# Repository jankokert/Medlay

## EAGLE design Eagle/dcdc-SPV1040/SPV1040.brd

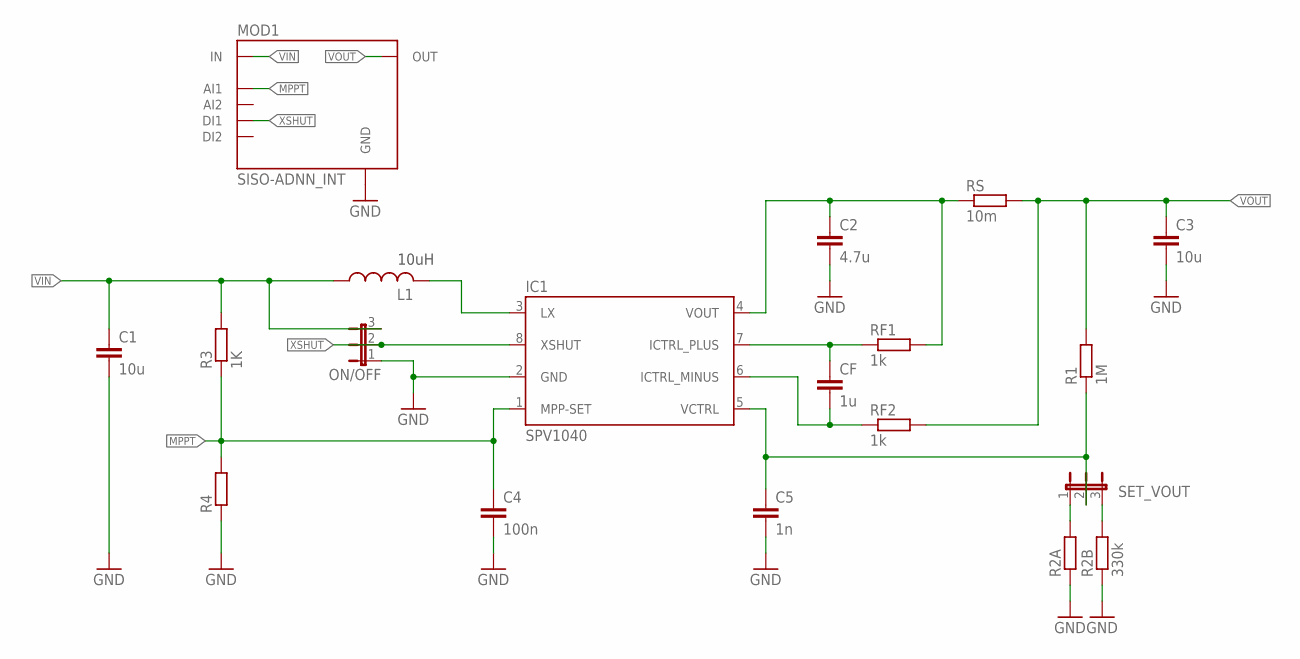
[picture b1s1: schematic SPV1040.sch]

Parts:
C1, C3: 10u; C0805
C2: 4.7u; C0805
C4: 100n; C0805
C5: 1n; C0805
CF: 1u; C0805
IC1: SPV1040; TSSOP8
L1: IHLP-2525CZ-01; 2525
MOD1: SISO-ADNN_INT; SISO-ADNN
ON/OFF: JP2E; JP2
R1: 1M; R0805
R2A, R4: R-EU_R0805; R0805
R2B: 330k; R0805
R3: 1K; R0805
RF1, RF2: 1k; R0805
RS: 10m; R0805
SET_VOUT: JP2E; JP2

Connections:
GND: C1.2, C2.2, C3.2, C4.2, C5.2, IC1.2 (GND), MOD1.GND1 (GND), MOD1.GND2 (GND), MOD1.GND3 (GND), MOD1.GND4 (GND), ON/OFF.1, R2A.1, R2B.1, R4.1
MPPT: C4.1, IC1.1 (MPP-SET), MOD1.AI1, R3.1, R4.2
unnamed: IC1.3 (LX), L1.P$1
unnamed: CF.2, IC1.6 (ICTRL_MINUS), RF2.1
unnamed: CF.1, IC1.7 (ICTRL_PLUS), RF1.1
unnamed: C2.1, IC1.4 (VOUT), RF1.2, RS.1
unnamed: C5.1, IC1.5 (VCTRL), R1.1, SET_VOUT.2
unnamed: R2A.2, SET_VOUT.1
unnamed: R2B.2, SET_VOUT.3
VIN: C1.1, L1.P$2, MOD1.IN1 (IN), MOD1.IN2 (IN), MOD1.IN3 (IN), MOD1.IN4 (IN), ON/OFF.3, R3.2
VOUT: C3.1, MOD1.OUT1_1 (OUT), MOD1.OUT1_2 (OUT), MOD1.OUT1_3 (OUT), MOD1.OUT1_4 (OUT), R1.2, RF2.2, RS.2
XSHUT: IC1.8 (XSHUT), MOD1.DI1, ON/OFF.2

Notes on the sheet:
10uH

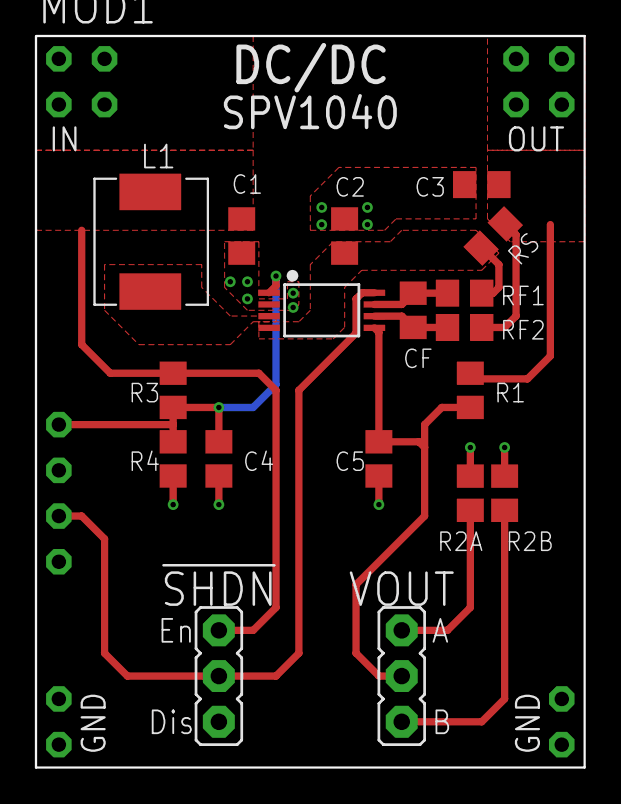
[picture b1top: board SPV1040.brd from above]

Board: 2 copper layers, 30.5 x 40.6 mm, 19 parts (0 on the bottom side), 12 nets.

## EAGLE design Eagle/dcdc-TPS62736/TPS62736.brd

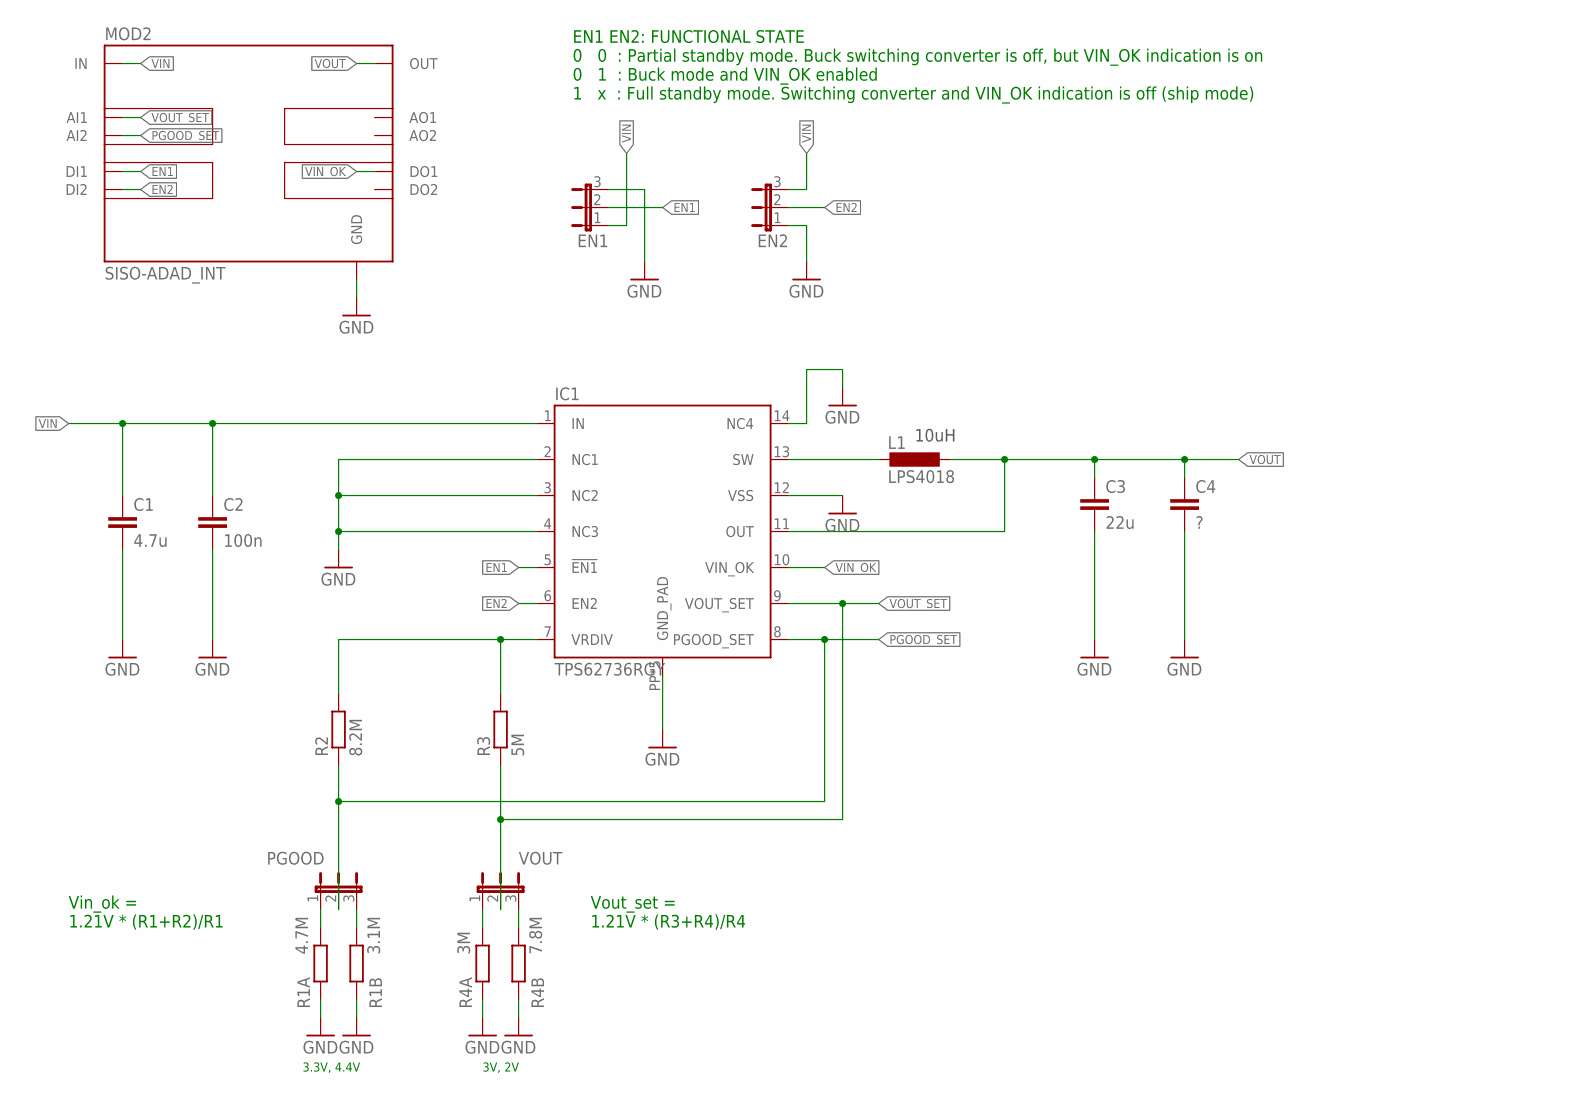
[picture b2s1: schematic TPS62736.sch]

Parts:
C1: 4.7u; C0805
C2: 100n; C0805
C3: 22u; C0805
C4: ?; C0805
EN1, EN2: JP2E; JP2
IC1: TPS62736RGY; S-PVQFN-N14
L1: LPS4018
MOD2: SISO-ADAD_INT; SISO-ADAD
PGOOD: JP2E; JP2
R1A: 4.7M; R0805
R1B: 3.1M; R0805
R2: 8.2M; R0805
R3: 5M; R0805
R4A: 3M; R0805
R4B: 7.8M; R0805
VOUT: JP2E; JP2

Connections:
EN1: EN1.2, IC1.5 (!EN1), MOD2.DI1
EN2: EN2.2, IC1.6 (EN2), MOD2.DI2
GND: C1.2, C2.2, C3.2, C4.2, EN1.3, EN2.1, IC1.2 (NC1), IC1.3 (NC2), IC1.4 (NC3), IC1.12 (VSS), IC1.14 (NC4), IC1.PP (GND_PAD), IC1.PP@1 (GND_PAD), IC1.PP@2 (GND_PAD), IC1.PP@3 (GND_PAD), IC1.PP@4 (GND_PAD), MOD2.GND1 (GND), MOD2.GND2 (GND), MOD2.GND3 (GND), MOD2.GND4 (GND), R1A.1, R1B.1, R4A.1, R4B.1
unnamed: IC1.7 (VRDIV), R2.2, R3.2
unnamed: IC1.13 (SW), L1.1
unnamed: R4A.2, VOUT.1
unnamed: R4B.2, VOUT.3
unnamed: PGOOD.1, R1A.2
unnamed: PGOOD.3, R1B.2
PGOOD_SET: IC1.8 (PGOOD_SET), MOD2.AI2, PGOOD.2, R2.1
VIN: C1.1, C2.1, EN1.1, EN2.3, IC1.1 (IN), MOD2.IN1 (IN), MOD2.IN2 (IN), MOD2.IN3 (IN), MOD2.IN4 (IN)
VIN_OK: IC1.10 (VIN_OK), MOD2.DO1
VOUT: C3.1, C4.1, IC1.11 (OUT), L1.2, MOD2.OUT1_1 (OUT), MOD2.OUT1_2 (OUT), MOD2.OUT1_3 (OUT), MOD2.OUT1_4 (OUT)
VOUT_SET: IC1.9 (VOUT_SET), MOD2.AI1, R3.1, VOUT.2

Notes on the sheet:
10uH
EN1 EN2: FUNCTIONAL STATE 0 0 : Partial standby mode. Buck switching converter is off, but VIN_OK indication is on 0 1 : Buck mode and VIN_OK enabled 1 x : Full standby mode. Switching converter and VIN_OK indication is off (ship mode)
Vin_ok = 1.21V * (R1+R2)/R1
Vout_set = 1.21V * (R3+R4)/R4
3V, 2V
3.3V, 4.4V

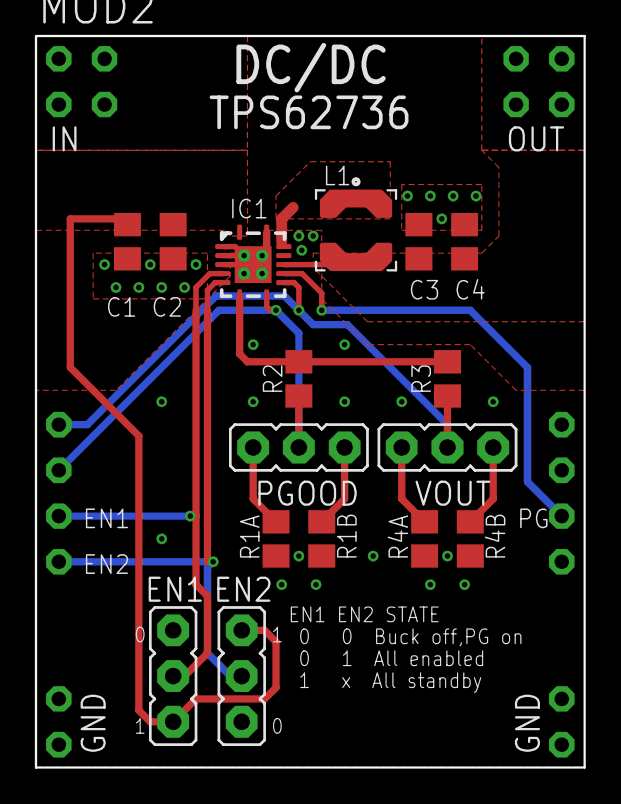
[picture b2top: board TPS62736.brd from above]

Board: 2 copper layers, 30.5 x 40.6 mm, 17 parts (0 on the bottom side), 14 nets.

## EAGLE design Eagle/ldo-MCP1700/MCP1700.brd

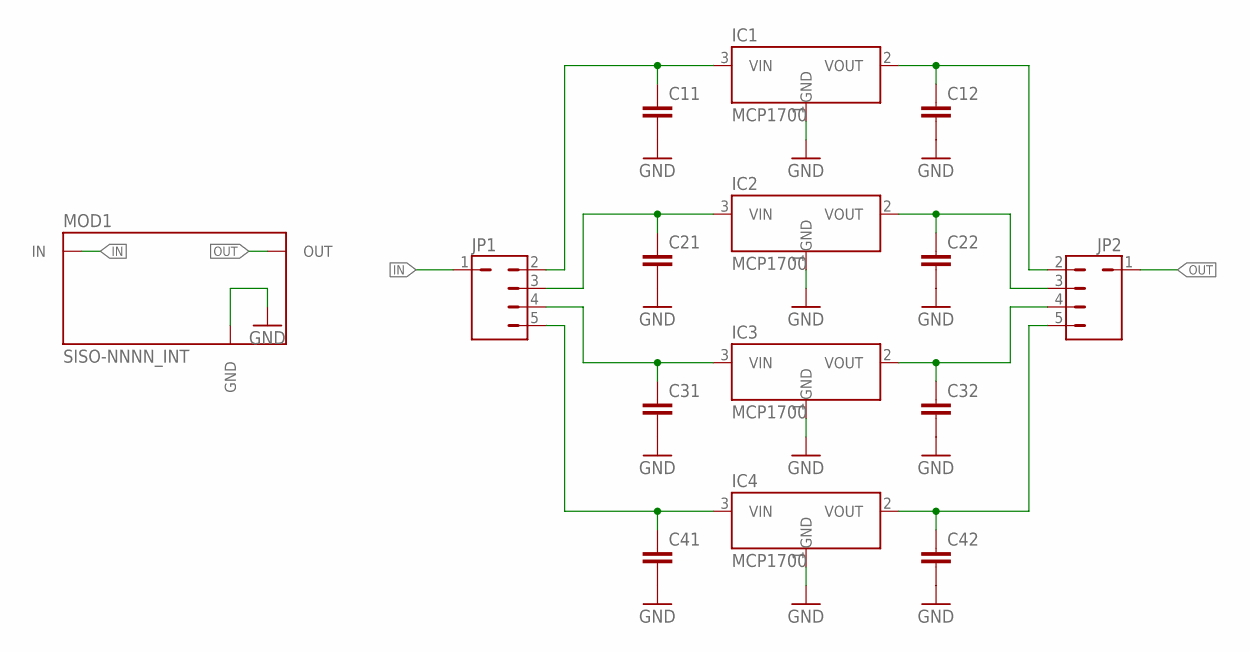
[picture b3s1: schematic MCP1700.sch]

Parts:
C11, C12, C21, C22, C31, C32, C41, C42: C-EUC0805; C0805
IC1, IC2, IC3, IC4: MCP1700; SOT23
JP1, JP2: JP4Q; JP1-4
MOD1: SISO-NNNN_INT; SISO-NNNN

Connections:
GND: C11.2, C12.2, C21.2, C22.2, C31.2, C32.2, C41.2, C42.2, IC1.1 (GND), IC2.1 (GND), IC3.1 (GND), IC4.1 (GND), MOD1.GND1 (GND), MOD1.GND2 (GND), MOD1.GND3 (GND), MOD1.GND4 (GND)
IN: JP1.1, MOD1.IN1 (IN), MOD1.IN2 (IN), MOD1.IN3 (IN), MOD1.IN4 (IN)
unnamed: C11.1, IC1.3 (VIN), JP1.2
unnamed: C21.1, IC2.3 (VIN), JP1.3
unnamed: C31.1, IC3.3 (VIN), JP1.4
unnamed: C41.1, IC4.3 (VIN), JP1.5
unnamed: C12.1, IC1.2 (VOUT), JP2.2
unnamed: C22.1, IC2.2 (VOUT), JP2.3
unnamed: C32.1, IC3.2 (VOUT), JP2.4
unnamed: C42.1, IC4.2 (VOUT), JP2.5
OUT: JP2.1, MOD1.OUT1 (OUT), MOD1.OUT2 (OUT), MOD1.OUT3 (OUT), MOD1.OUT4 (OUT)

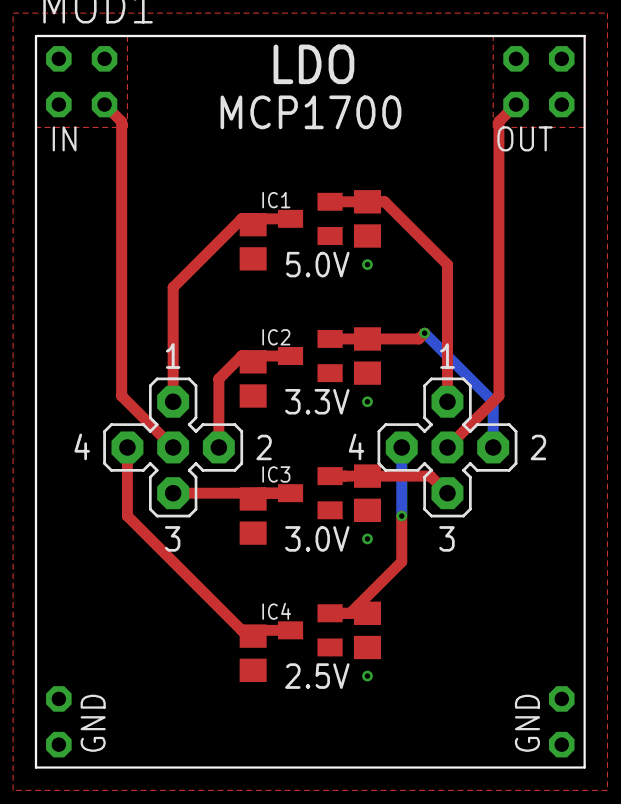
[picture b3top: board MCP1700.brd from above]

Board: 2 copper layers, 30.5 x 40.6 mm, 15 parts (0 on the bottom side), 11 nets.

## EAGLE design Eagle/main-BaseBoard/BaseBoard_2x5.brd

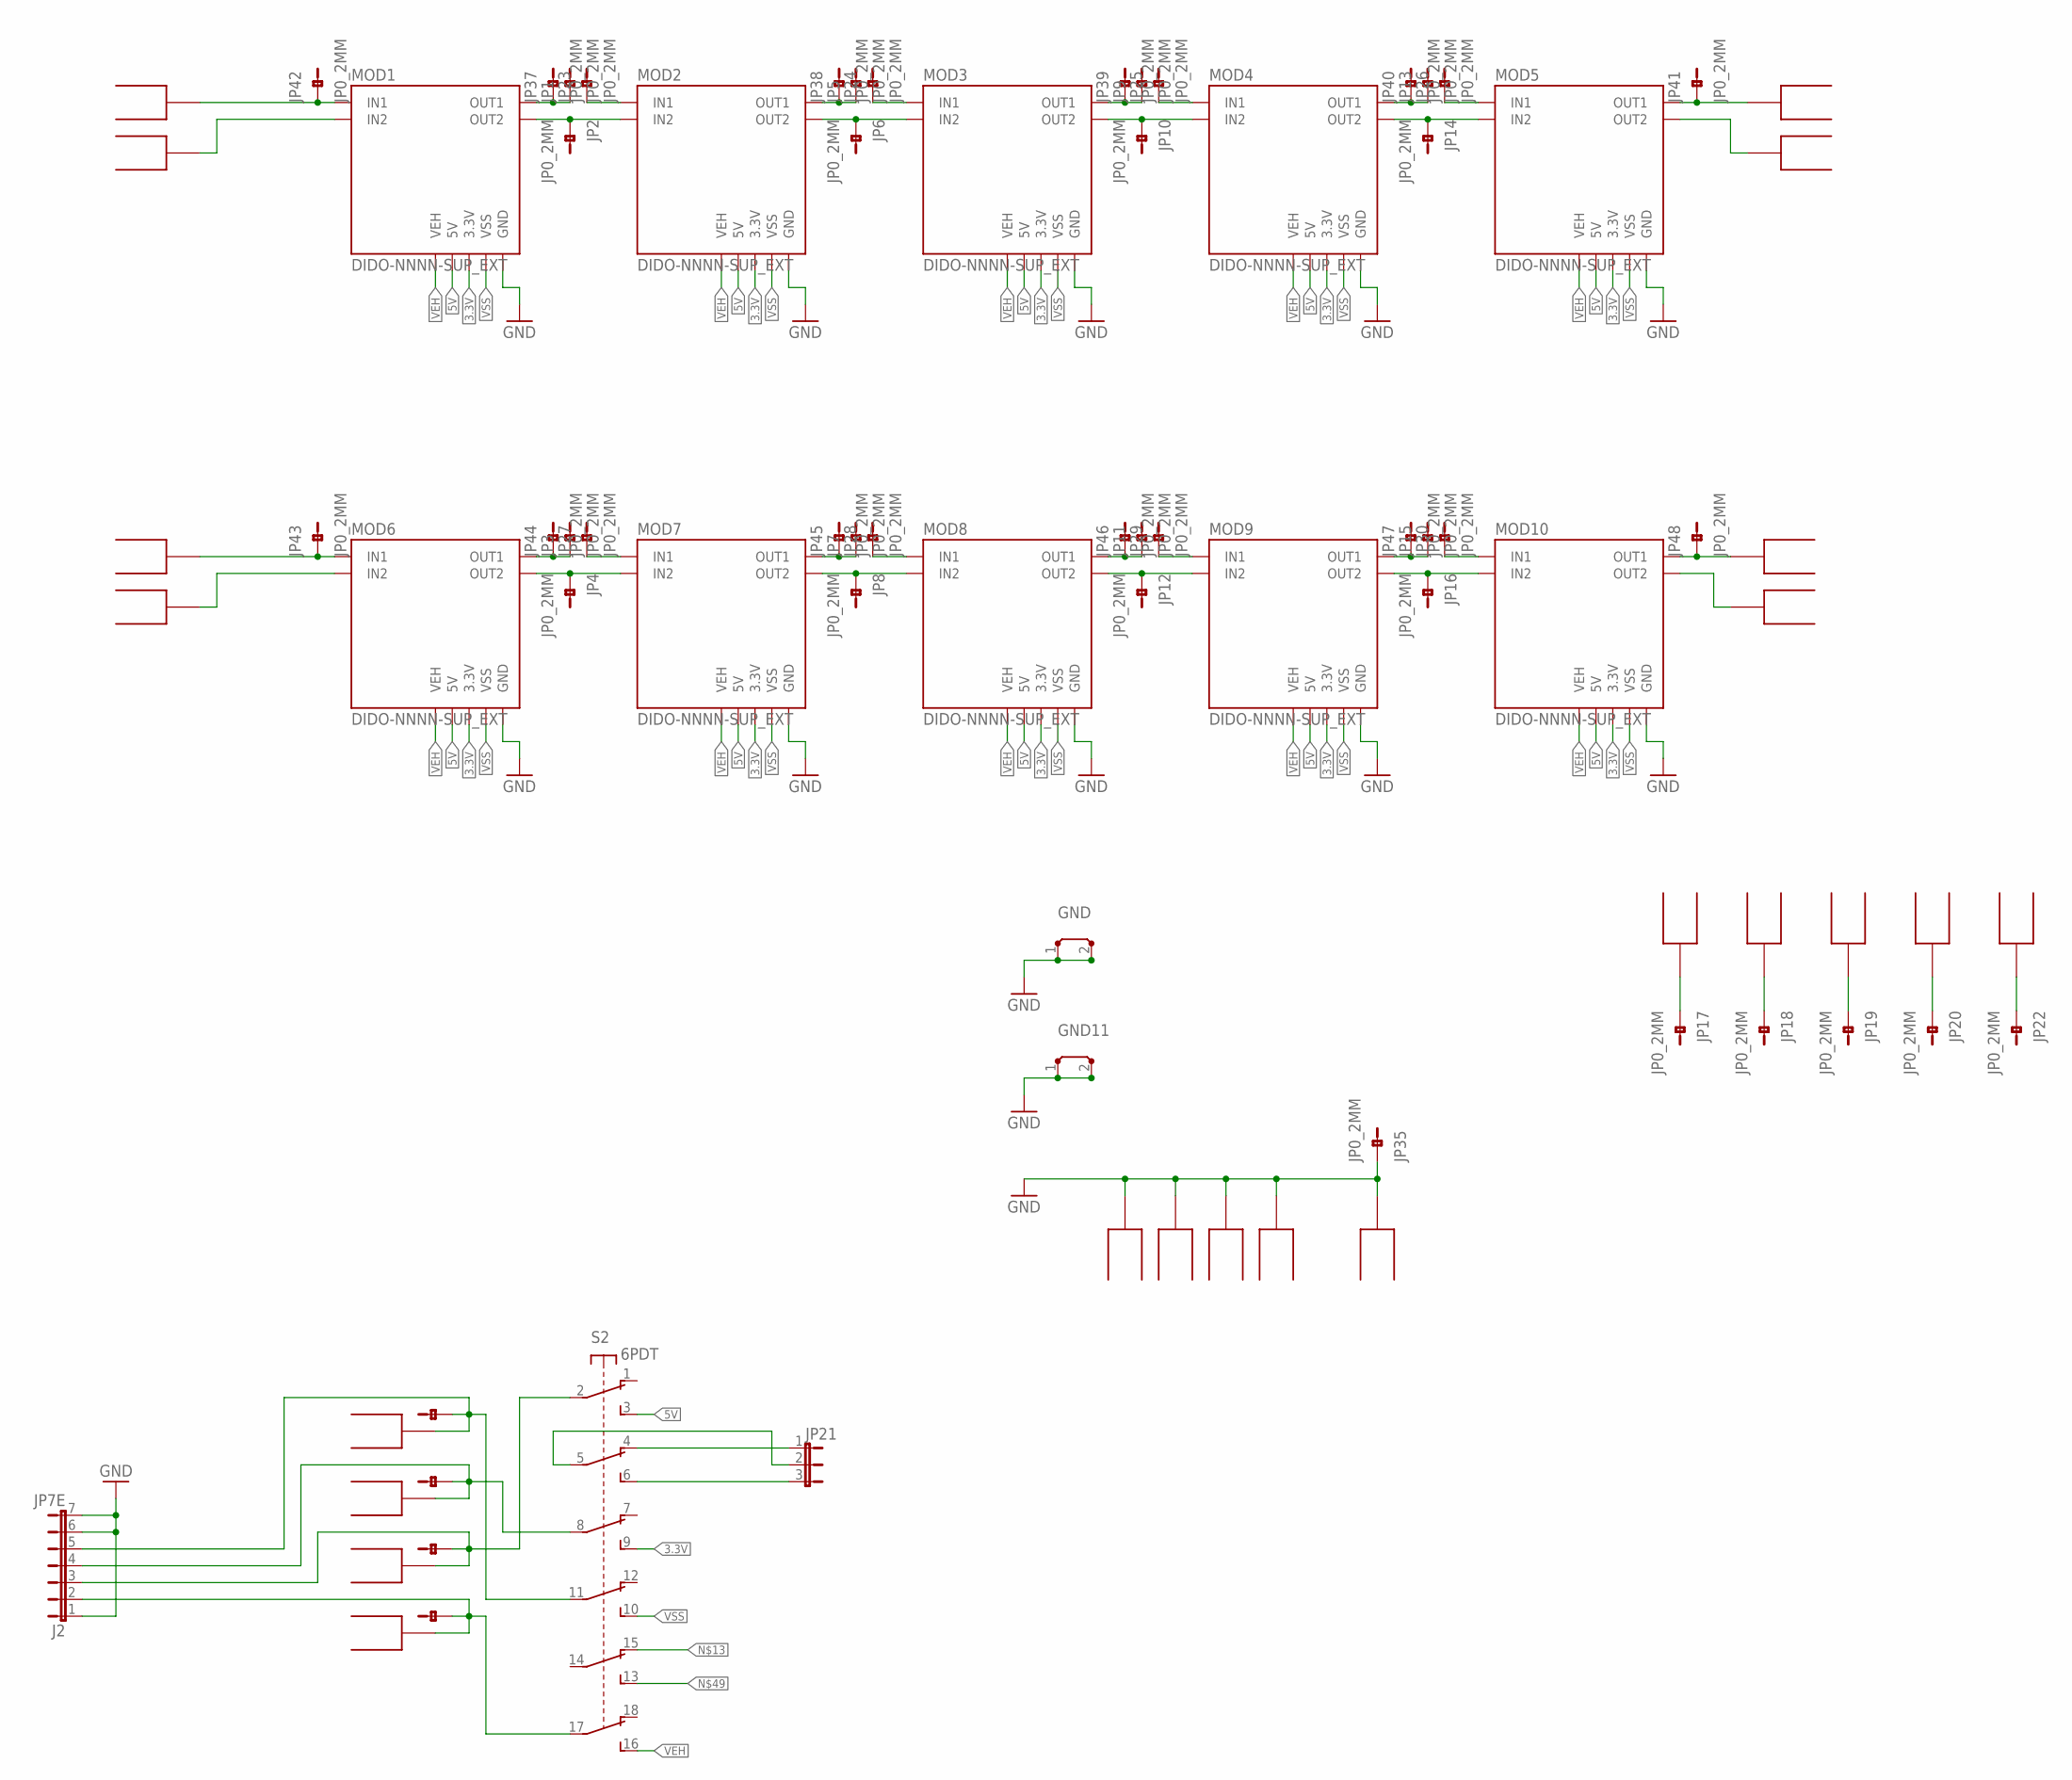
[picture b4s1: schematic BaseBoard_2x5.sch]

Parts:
GND, GND11: TE4/2
J2: JP7E; JP7
JP1, JP2, JP3, JP4, JP5, JP6, JP7, JP8, JP9, JP10, JP11, JP12, JP13, JP14, JP15, JP16, JP17, JP18, JP19, JP20, JP22, JP23, JP24, JP25, JP26, JP27, JP28, JP29, JP30, JP35, JP37, JP38, JP39, JP40, JP41, JP42, JP43, JP44, JP45, JP46, JP47, JP48, JP53, JP54, JP55, JP56: JP0_2MM; JP0-2MM
JP21: JP2E; JP2
MOD1, MOD2, MOD3, MOD4, MOD5, MOD6, MOD7, MOD8, MOD9, MOD10: DIDO-NNNN-SUP_EXT
MODULE1, MODULE2, MODULE3, MODULE4, MODULE5, MODULE6, MODULE7, MODULE8, MODULE9, MODULE10: MODULE_OVERLAY
P1, P2, P3, P4, P5, P6, P10, P11, P12, P13, P14, P15, P16, P18, P19, P20, P21, P22, P23, P24, P27, P28: BANANA-PLUGROUND; 6MM-PAD-ROUND
S2: 6PDT; DIL18

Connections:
3.3V: MOD1.3.3V, MOD2.3.3V, MOD3.3.3V, MOD4.3.3V, MOD5.3.3V, MOD6.3.3V, MOD7.3.3V, MOD8.3.3V, MOD9.3.3V, MOD10.3.3V, S2.9 (S3)
5V: MOD1.5V, MOD2.5V, MOD3.5V, MOD4.5V, MOD5.5V, MOD6.5V, MOD7.5V, MOD8.5V, MOD9.5V, MOD10.5V, S2.3 (S1)
GND: GND.1, GND.2, GND11.1, GND11.2, J2.1, J2.6, J2.7, JP35.1, MOD1.GND1 (GND), MOD1.GND2 (GND), MOD1.GND3 (GND), MOD1.GND4 (GND), MOD2.GND1 (GND), MOD2.GND2 (GND), MOD2.GND3 (GND), MOD2.GND4 (GND), MOD3.GND1 (GND), MOD3.GND2 (GND), MOD3.GND3 (GND), MOD3.GND4 (GND), MOD4.GND1 (GND), MOD4.GND2 (GND), MOD4.GND3 (GND), MOD4.GND4 (GND), MOD5.GND1 (GND), MOD5.GND2 (GND), MOD5.GND3 (GND), MOD5.GND4 (GND), MOD6.GND1 (GND), MOD6.GND2 (GND), MOD6.GND3 (GND), MOD6.GND4 (GND), MOD7.GND1 (GND), MOD7.GND2 (GND), MOD7.GND3 (GND), MOD7.GND4 (GND), MOD8.GND1 (GND), MOD8.GND2 (GND), MOD8.GND3 (GND), MOD8.GND4 (GND), MOD9.GND1 (GND), MOD9.GND2 (GND), MOD9.GND3 (GND), MOD9.GND4 (GND), MOD10.GND1 (GND), MOD10.GND2 (GND), MOD10.GND3 (GND), MOD10.GND4 (GND), P5.1, P14.1, P15.1, P16.1, P18.1
unnamed: MOD5.OUT2_1 (OUT2), MOD5.OUT2_2 (OUT2), MOD5.OUT2_3 (OUT2), MOD5.OUT2_4 (OUT2), P11.1
unnamed: JP42.1, MOD1.IN1, MOD1.IN2 (IN1), MOD1.IN3 (IN1), MOD1.IN4 (IN1), P1.1
unnamed: MOD10.OUT2_1 (OUT2), MOD10.OUT2_2 (OUT2), MOD10.OUT2_3 (OUT2), MOD10.OUT2_4 (OUT2), P13.1
unnamed: MOD1.IN2_1 (IN2), MOD1.IN2_2 (IN2), MOD1.IN2_3 (IN2), MOD1.IN2_4 (IN2), P2.1
unnamed: JP1.1, JP37.1, MOD1.OUT1, MOD1.OUT2 (OUT1), MOD1.OUT3 (OUT1), MOD1.OUT4 (OUT1)
unnamed: JP5.1, JP38.1, MOD2.OUT1, MOD2.OUT2 (OUT1), MOD2.OUT3 (OUT1), MOD2.OUT4 (OUT1)
unnamed: JP2.1, MOD1.OUT2_1 (OUT2), MOD1.OUT2_2 (OUT2), MOD1.OUT2_3 (OUT2), MOD1.OUT2_4 (OUT2), MOD2.IN2_1 (IN2), MOD2.IN2_2 (IN2), MOD2.IN2_3 (IN2), MOD2.IN2_4 (IN2)
unnamed: JP17.1, P19.1
unnamed: JP9.1, JP39.1, MOD3.OUT1, MOD3.OUT2 (OUT1), MOD3.OUT3 (OUT1), MOD3.OUT4 (OUT1)
unnamed: JP41.1, MOD5.OUT1, MOD5.OUT2 (OUT1), MOD5.OUT3 (OUT1), MOD5.OUT4 (OUT1), P10.1
unnamed: JP6.1, MOD2.OUT2_1 (OUT2), MOD2.OUT2_2 (OUT2), MOD2.OUT2_3 (OUT2), MOD2.OUT2_4 (OUT2), MOD3.IN2_1 (IN2), MOD3.IN2_2 (IN2), MOD3.IN2_3 (IN2), MOD3.IN2_4 (IN2)
unnamed: JP18.1, P20.1
unnamed: J2.3, JP54.1, P27.1, S2.2 (P1), S2.15 (O5)
unnamed: JP23.1, MOD2.IN1, MOD2.IN2 (IN1), MOD2.IN3 (IN1), MOD2.IN4 (IN1)
unnamed: JP10.1, MOD3.OUT2_1 (OUT2), MOD3.OUT2_2 (OUT2), MOD3.OUT2_3 (OUT2), MOD3.OUT2_4 (OUT2), MOD4.IN2_1 (IN2), MOD4.IN2_2 (IN2), MOD4.IN2_3 (IN2), MOD4.IN2_4 (IN2)
unnamed: JP19.1, P21.1
unnamed: JP48.1, MOD10.OUT1, MOD10.OUT2 (OUT1), MOD10.OUT3 (OUT1), MOD10.OUT4 (OUT1), P12.1
unnamed: JP16.1, MOD9.OUT2_1 (OUT2), MOD9.OUT2_2 (OUT2), MOD9.OUT2_3 (OUT2), MOD9.OUT2_4 (OUT2), MOD10.IN2_1 (IN2), MOD10.IN2_2 (IN2), MOD10.IN2_3 (IN2), MOD10.IN2_4 (IN2)
unnamed: JP14.1, MOD4.OUT2_1 (OUT2), MOD4.OUT2_2 (OUT2), MOD4.OUT2_3 (OUT2), MOD4.OUT2_4 (OUT2), MOD5.IN2_1 (IN2), MOD5.IN2_2 (IN2), MOD5.IN2_3 (IN2), MOD5.IN2_4 (IN2)
unnamed: JP13.1, JP40.1, MOD4.OUT1, MOD4.OUT2 (OUT1), MOD4.OUT3 (OUT1), MOD4.OUT4 (OUT1)
unnamed: JP20.1, P22.1
unnamed: JP21.3, S2.6 (S2)
unnamed: JP21.1, S2.4 (O2)
unnamed: JP21.2, S2.5 (P2)
unnamed: MOD6.IN2_1 (IN2), MOD6.IN2_2 (IN2), MOD6.IN2_3 (IN2), MOD6.IN2_4 (IN2), P4.1
unnamed: JP4.1, MOD6.OUT2_1 (OUT2), MOD6.OUT2_2 (OUT2), MOD6.OUT2_3 (OUT2), MOD6.OUT2_4 (OUT2), MOD7.IN2_1 (IN2), MOD7.IN2_2 (IN2), MOD7.IN2_3 (IN2), MOD7.IN2_4 (IN2)
unnamed: JP26.1, MOD5.IN1, MOD5.IN2 (IN1), MOD5.IN3 (IN1), MOD5.IN4 (IN1)
unnamed: JP22.1, P6.1
unnamed: JP25.1, MOD4.IN1, MOD4.IN2 (IN1), MOD4.IN3 (IN1), MOD4.IN4 (IN1)
unnamed: JP8.1, MOD7.OUT2_1 (OUT2), MOD7.OUT2_2 (OUT2), MOD7.OUT2_3 (OUT2), MOD7.OUT2_4 (OUT2), MOD8.IN2_1 (IN2), MOD8.IN2_2 (IN2), MOD8.IN2_3 (IN2), MOD8.IN2_4 (IN2)
unnamed: JP24.1, MOD3.IN1, MOD3.IN2 (IN1), MOD3.IN3 (IN1), MOD3.IN4 (IN1)
unnamed: JP12.1, MOD8.OUT2_1 (OUT2), MOD8.OUT2_2 (OUT2), MOD8.OUT2_3 (OUT2), MOD8.OUT2_4 (OUT2), MOD9.IN2_1 (IN2), MOD9.IN2_2 (IN2), MOD9.IN2_3 (IN2), MOD9.IN2_4 (IN2)
unnamed: J2.2, JP53.1, P28.1, S2.17 (P6)
unnamed: JP27.1, MOD7.IN1, MOD7.IN2 (IN1), MOD7.IN3 (IN1), MOD7.IN4 (IN1)
unnamed: JP28.1, MOD8.IN1, MOD8.IN2 (IN1), MOD8.IN3 (IN1), MOD8.IN4 (IN1)
unnamed: JP29.1, MOD9.IN1, MOD9.IN2 (IN1), MOD9.IN3 (IN1), MOD9.IN4 (IN1)
unnamed: JP30.1, MOD10.IN1, MOD10.IN2 (IN1), MOD10.IN3 (IN1), MOD10.IN4 (IN1)
unnamed: JP43.1, MOD6.IN1, MOD6.IN2 (IN1), MOD6.IN3 (IN1), MOD6.IN4 (IN1), P3.1
unnamed: JP3.1, JP44.1, MOD6.OUT1, MOD6.OUT2 (OUT1), MOD6.OUT3 (OUT1), MOD6.OUT4 (OUT1)
unnamed: JP7.1, JP45.1, MOD7.OUT1, MOD7.OUT2 (OUT1), MOD7.OUT3 (OUT1), MOD7.OUT4 (OUT1)
unnamed: JP11.1, JP46.1, MOD8.OUT1, MOD8.OUT2 (OUT1), MOD8.OUT3 (OUT1), MOD8.OUT4 (OUT1)
unnamed: JP15.1, JP47.1, MOD9.OUT1, MOD9.OUT2 (OUT1), MOD9.OUT3 (OUT1), MOD9.OUT4 (OUT1)
unnamed: J2.4, JP55.1, P24.1, S2.8 (P3), S2.13 (S5)
unnamed: J2.5, JP56.1, P23.1, S2.11 (P4)
VEH: MOD1.VEH, MOD2.VEH, MOD3.VEH, MOD4.VEH, MOD5.VEH, MOD6.VEH, MOD7.VEH, MOD8.VEH, MOD9.VEH, MOD10.VEH, S2.16 (S6)
VSS: MOD1.VSS, MOD2.VSS, MOD3.VSS, MOD4.VSS, MOD5.VSS, MOD6.VSS, MOD7.VSS, MOD8.VSS, MOD9.VSS, MOD10.VSS, S2.10 (S4)

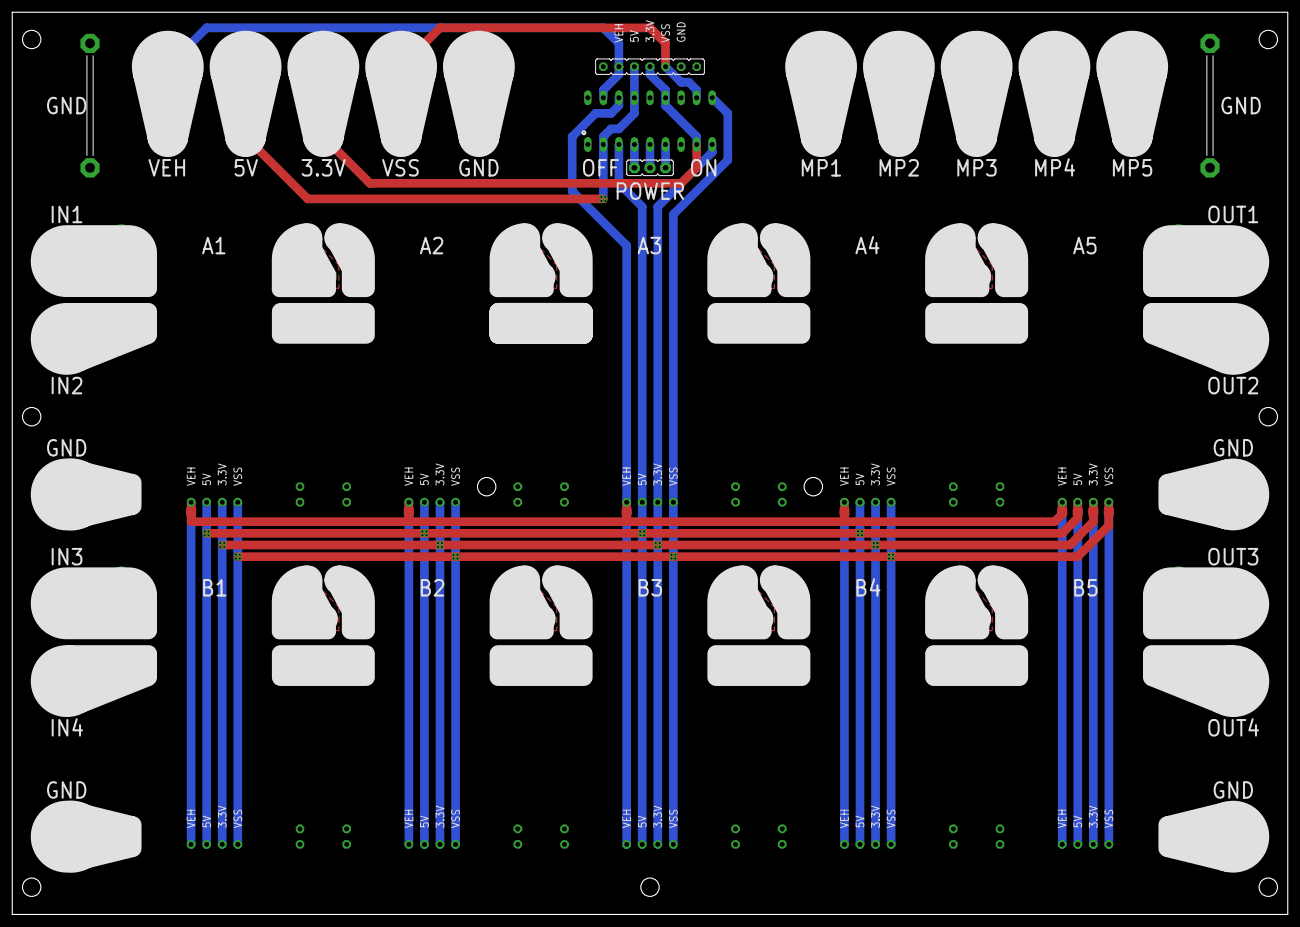
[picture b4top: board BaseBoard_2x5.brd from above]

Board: 2 copper layers, 208.3 x 147.3 mm, 93 parts (0 on the bottom side), 49 nets.

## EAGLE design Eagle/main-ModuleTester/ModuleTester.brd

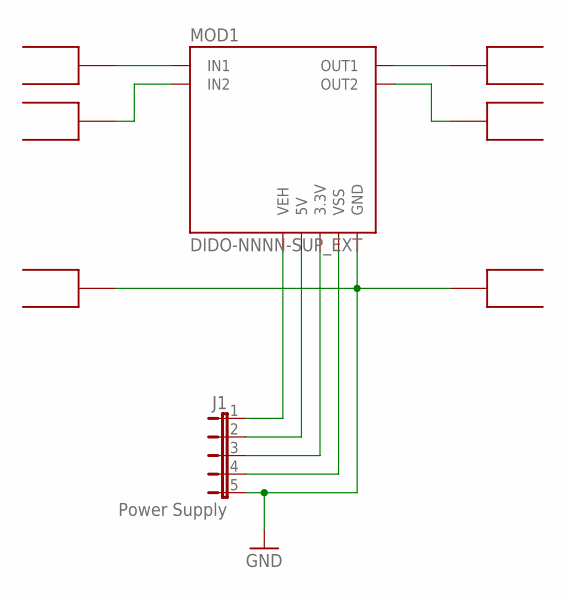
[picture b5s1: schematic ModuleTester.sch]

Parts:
J1: Power Supply; JP5
MOD1: DIDO-NNNN-SUP_EXT
U$1, U$2, U$3, U$4, U$5, U$6: BANANA-PLUGROUND; 6MM-PAD-ROUND

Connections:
GND: J1.5, MOD1.GND1 (GND), MOD1.GND2 (GND), MOD1.GND3 (GND), MOD1.GND4 (GND), U$5.1, U$6.1
IN1: MOD1.IN1, MOD1.IN2 (IN1), MOD1.IN3 (IN1), MOD1.IN4 (IN1), U$3.1
IN2: MOD1.IN2_1 (IN2), MOD1.IN2_2 (IN2), MOD1.IN2_3 (IN2), MOD1.IN2_4 (IN2), U$4.1
unnamed: J1.1, MOD1.VEH
unnamed: J1.2, MOD1.5V
unnamed: J1.3, MOD1.3.3V
unnamed: J1.4, MOD1.VSS
OUT1: MOD1.OUT1, MOD1.OUT2 (OUT1), MOD1.OUT3 (OUT1), MOD1.OUT4 (OUT1), U$1.1
OUT2: MOD1.OUT2_1 (OUT2), MOD1.OUT2_2 (OUT2), MOD1.OUT2_3 (OUT2), MOD1.OUT2_4 (OUT2), U$2.1

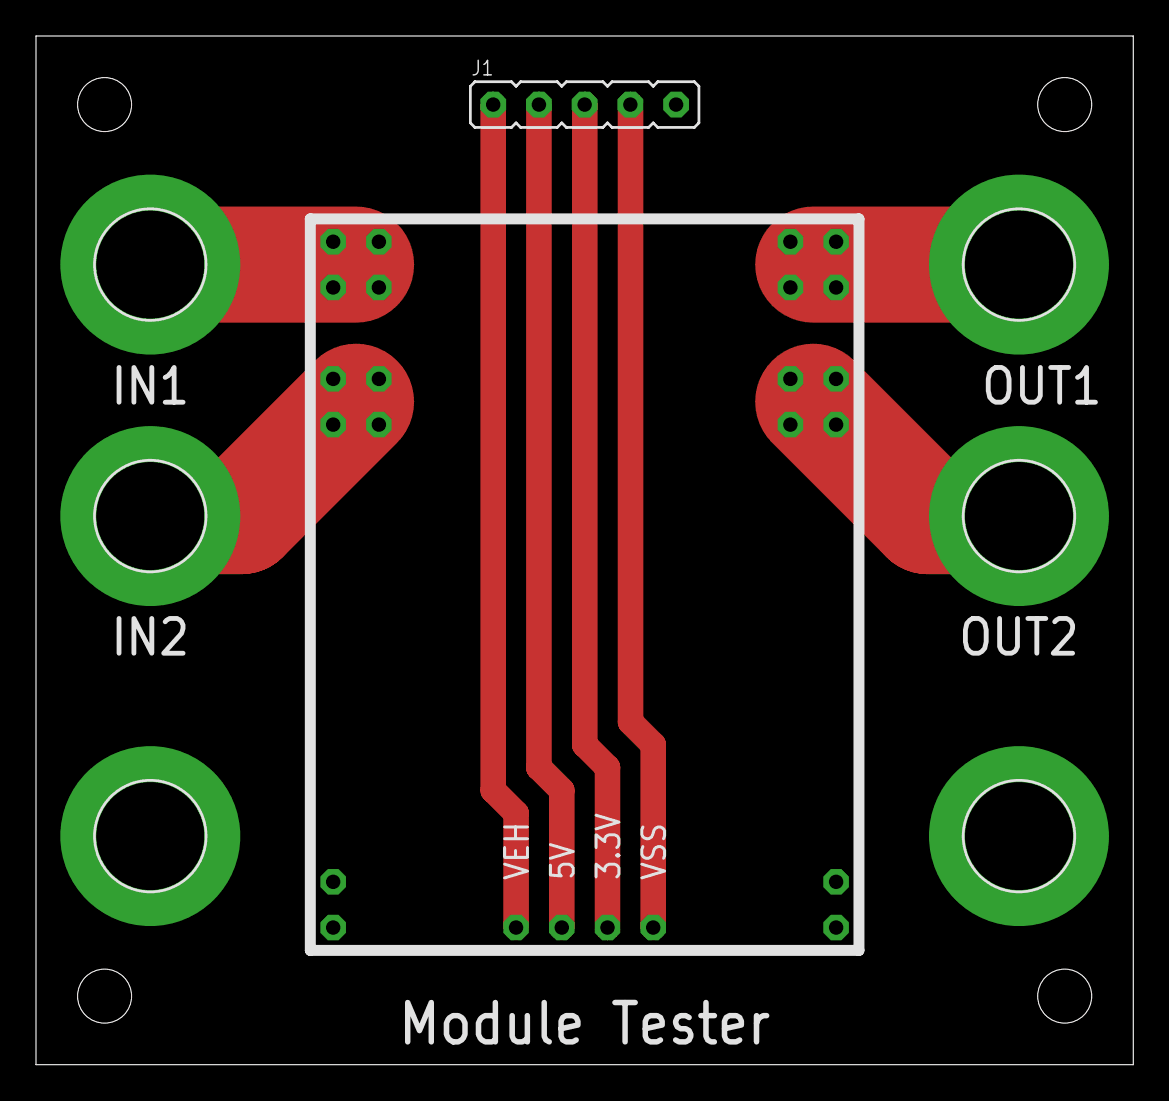
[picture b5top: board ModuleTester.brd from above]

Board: 2 copper layers, 61.0 x 57.1 mm, 9 parts (0 on the bottom side), 9 nets.

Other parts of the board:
U$7: MODULE_OVERLAY

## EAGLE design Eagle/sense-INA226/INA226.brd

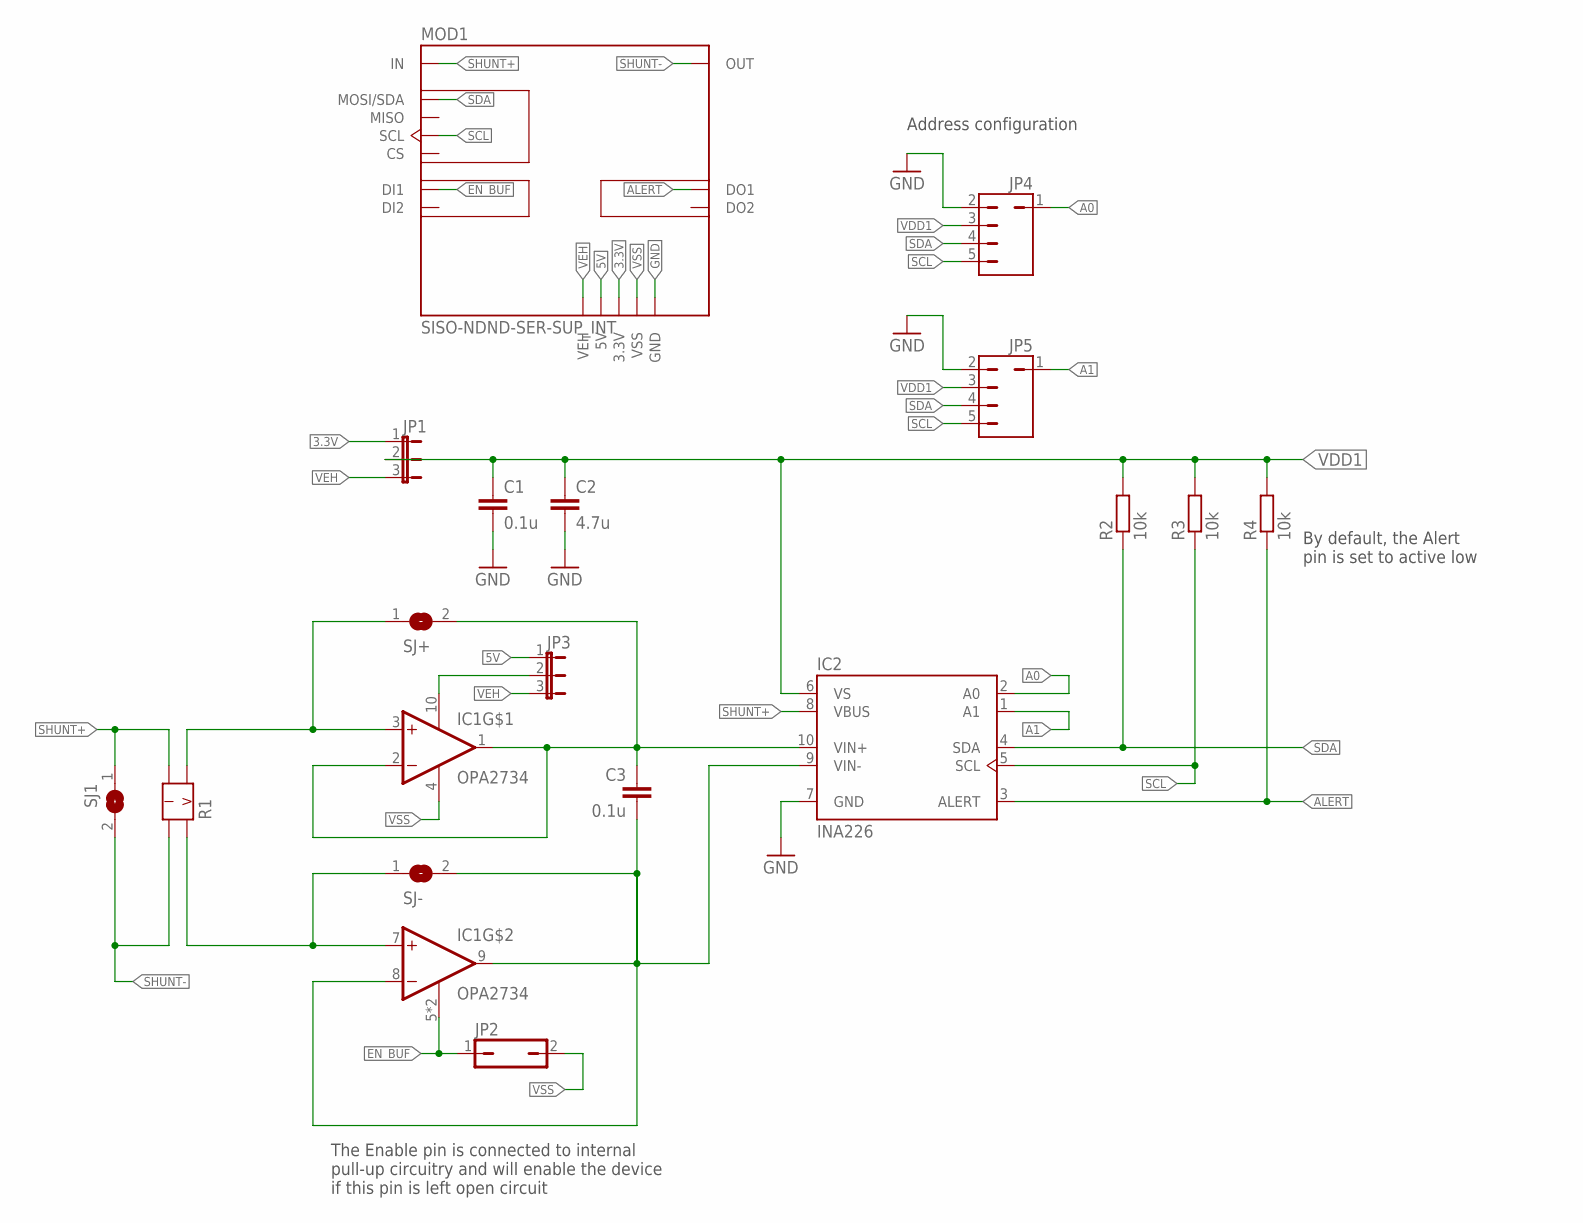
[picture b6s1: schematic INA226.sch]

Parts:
C1, C3: 0.1u; C0805K
C2: 4.7u; C1206K
IC1: OPA2734; MSOP10
IC2: INA226; DGS10
JP1, JP3: JP2E; JP2
JP2: JP1Q; JP1
JP4, JP5: JP3Q; JP1-4
MOD1: SISO-NDND-SER-SUP_INT; SISO-NDND-SER-SUP
R1: LVK_SERIESR1206; LVK12
R2, R3, R4: 10k; R0805
SJ1: SJ
SJ+: SJ2
SJ-: SJ2

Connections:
3.3V: JP1.1, MOD1.3.3V
5V: JP3.1, MOD1.5V
A0: IC2.2 (A0), JP4.1
A1: IC2.1 (A1), JP5.1
ALERT: IC2.3 (ALERT), MOD1.DO1, R4.1
EN_BUF: IC1.5 (EN$1), IC1.6 (EN$1), JP2.1, MOD1.DI1
GND: C1.2, C2.2, IC2.7 (GND), JP4.2, JP5.2, MOD1.GND1 (GND), MOD1.GND2 (GND), MOD1.GND3 (GND), MOD1.GND4 (GND)
unnamed: IC1.3 (+IN), R1.V2, SJ+.1
unnamed: IC1.10 (V+), JP3.2
unnamed: IC1.7 (+IN), R1.V1, SJ-.1
OUT_A: C3.1, IC1.1 (OUT), IC1.2 (-IN), IC2.10 (VIN+), SJ+.2
OUT_B: C3.2, IC1.8 (-IN), IC1.9 (OUT), IC2.9 (VIN-), SJ-.2
SCL: IC2.5 (SCL), JP4.5, JP5.5, MOD1.SCL, R3.1
SDA: IC2.4 (SDA), JP4.4, JP5.4, MOD1.MOSI/SDA, R2.1
SHUNT+: IC2.8 (VBUS), MOD1.IN1 (IN), MOD1.IN2 (IN), MOD1.IN3 (IN), MOD1.IN4 (IN), R1.I2, SJ1.1
SHUNT-: MOD1.OUT1 (OUT), MOD1.OUT2 (OUT), MOD1.OUT3 (OUT), MOD1.OUT4 (OUT), R1.I1, SJ1.2
VDD1: C1.1, C2.1, IC2.6 (VS), JP1.2, JP4.3, JP5.3, R2.2, R3.2, R4.2
VEH: JP1.3, JP3.3, MOD1.VEH
VSS: IC1.4 (V-), JP2.2, MOD1.VSS

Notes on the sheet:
Address configuration
By default, the Alert pin is set to active low
The Enable pin is connected to internal pull-up circuitry and will enable the device if this pin is left open circuit

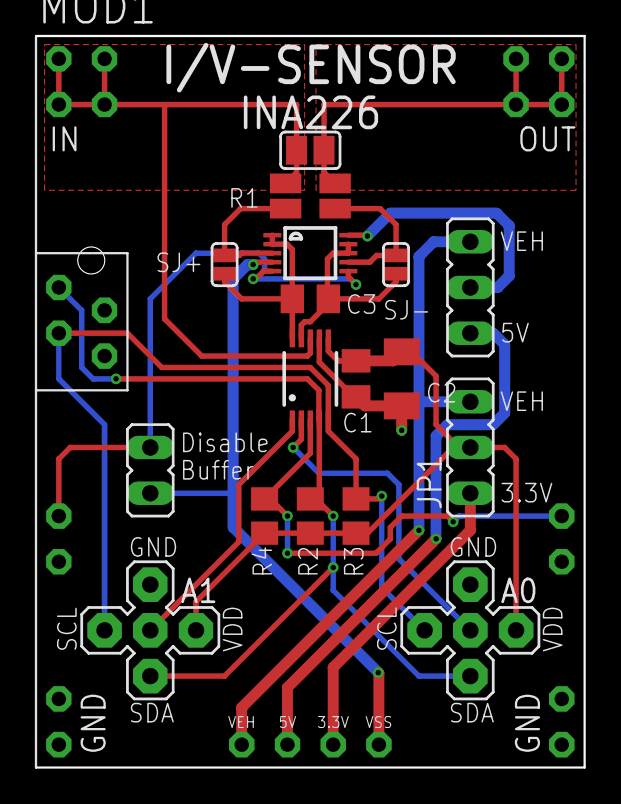
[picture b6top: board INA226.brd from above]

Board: 2 copper layers, 30.5 x 40.6 mm, 18 parts (0 on the bottom side), 19 nets.
